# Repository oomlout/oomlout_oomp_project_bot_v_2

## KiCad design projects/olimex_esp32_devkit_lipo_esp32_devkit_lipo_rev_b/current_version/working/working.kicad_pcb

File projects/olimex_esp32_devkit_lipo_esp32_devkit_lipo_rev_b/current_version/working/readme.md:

# esp32_devkit_lipo
 
## summary 
* id: olimex_esp32_devkit_lipo_esp32_devkit_lipo_rev_b
* user: olimex
* name: esp32_devkit_lipo
* board: esp32_devkit_lipo_rev_b
* repo: https://github.com/OLIMEX/ESP32-DevKit-LiPo
* src_file_repo_kicad_pcb: HARDWARE/ESP32-DevKit-LiPo-Rev.B/ESP32-DevKit-Lipo_Rev_B.kicad_pcb
* src_file_repo_kicad_pcb_link: https://github.com/OLIMEX/ESP32-DevKit-LiPo/tree/master/HARDWARE/ESP32-DevKit-LiPo-Rev.B/ESP32-DevKit-Lipo_Rev_B.kicad_pcb

* src_file_repo_sch: HARDWARE/ESP32-DevKit-LiPo-Rev.B/ESP32-DevKit-Lipo_Rev_B.sch
* src_file_repo_sch_link: https://github.com/OLIMEX/ESP32-DevKit-LiPo/tree/master/HARDWARE/ESP32-DevKit-LiPo-Rev.B/ESP32-DevKit-Lipo_Rev_B.sch
* full details link: https://github.com/oomlout/oomlout_oomp_project_bot_v_2/tree/main/projects/olimex_esp32_devkit_lipo_esp32_devkit_lipo_rev_b/current_version/working

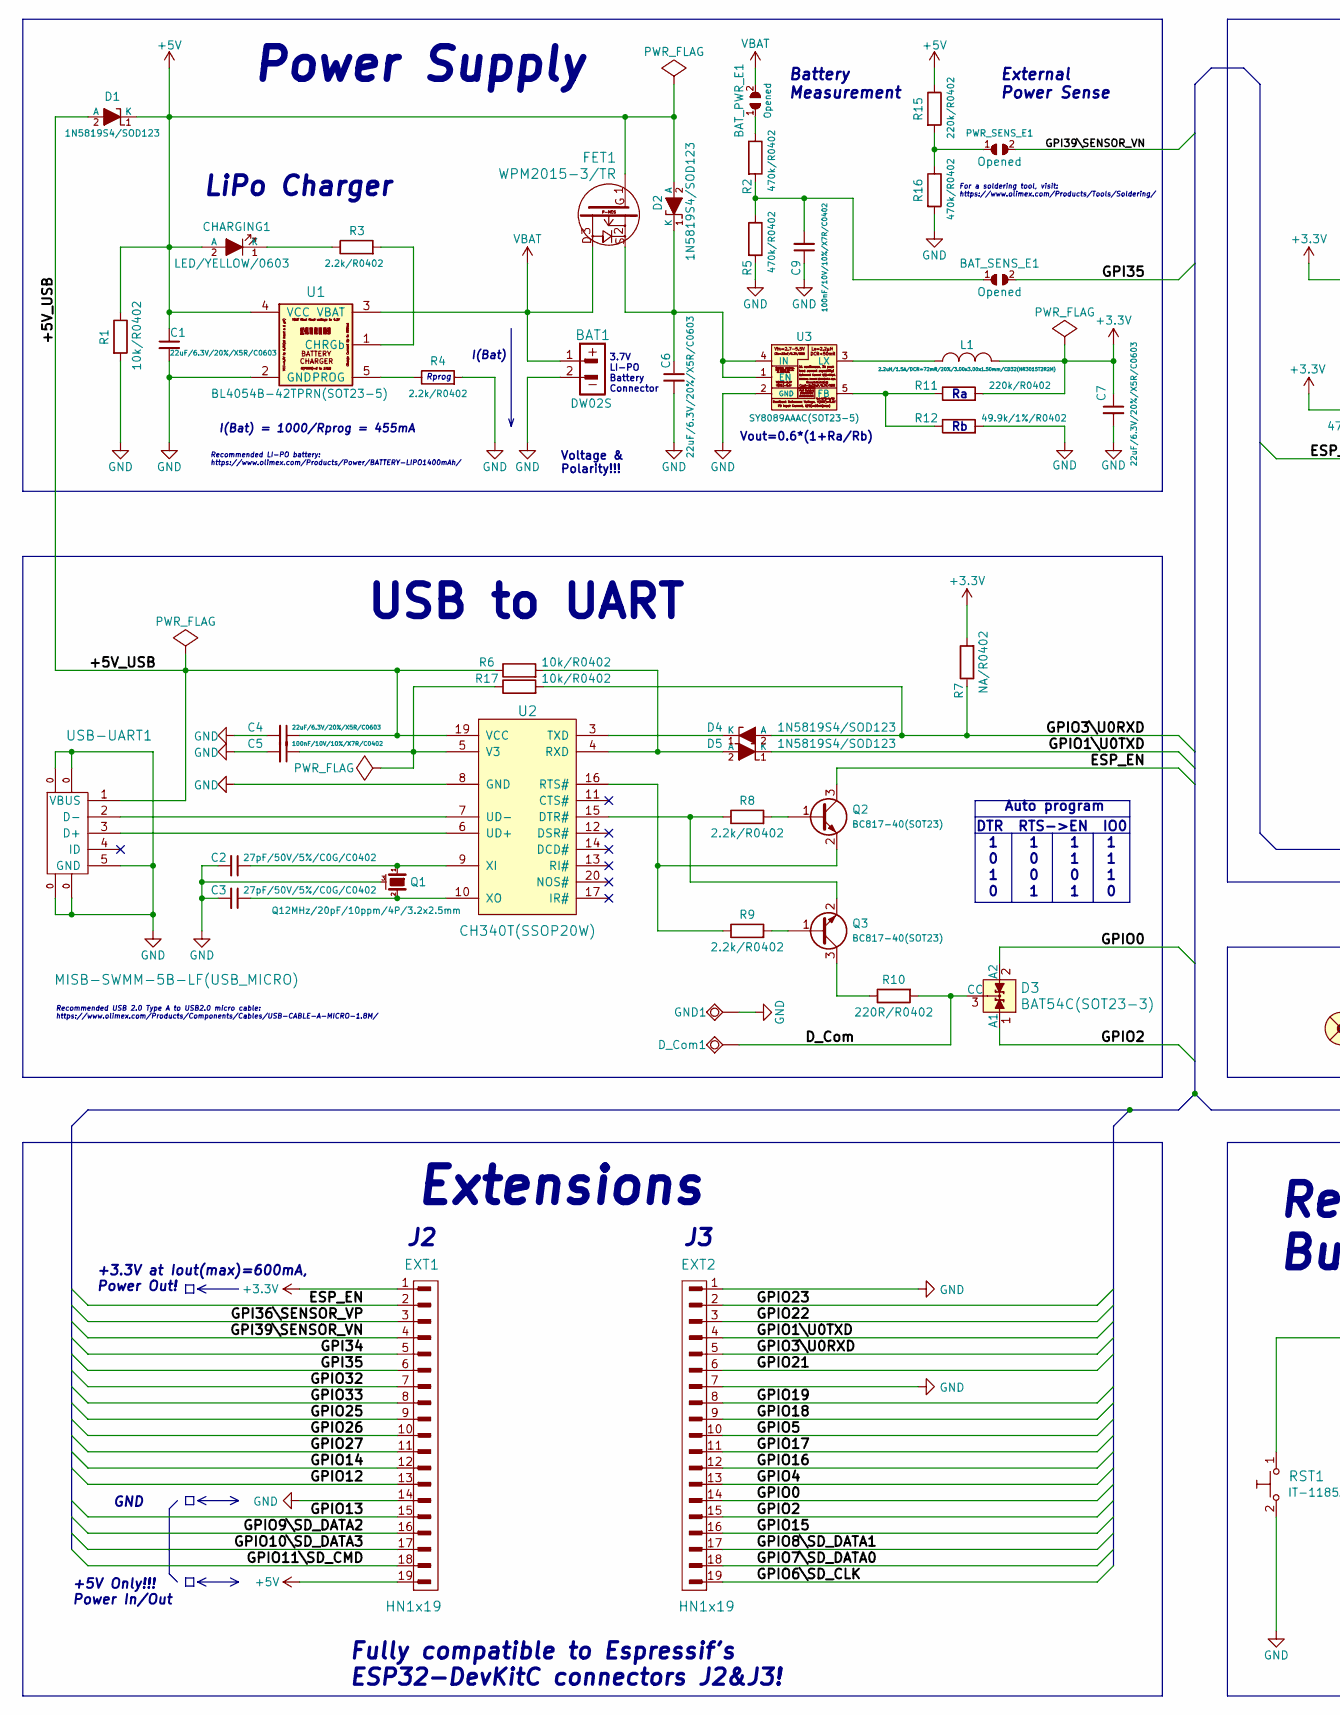
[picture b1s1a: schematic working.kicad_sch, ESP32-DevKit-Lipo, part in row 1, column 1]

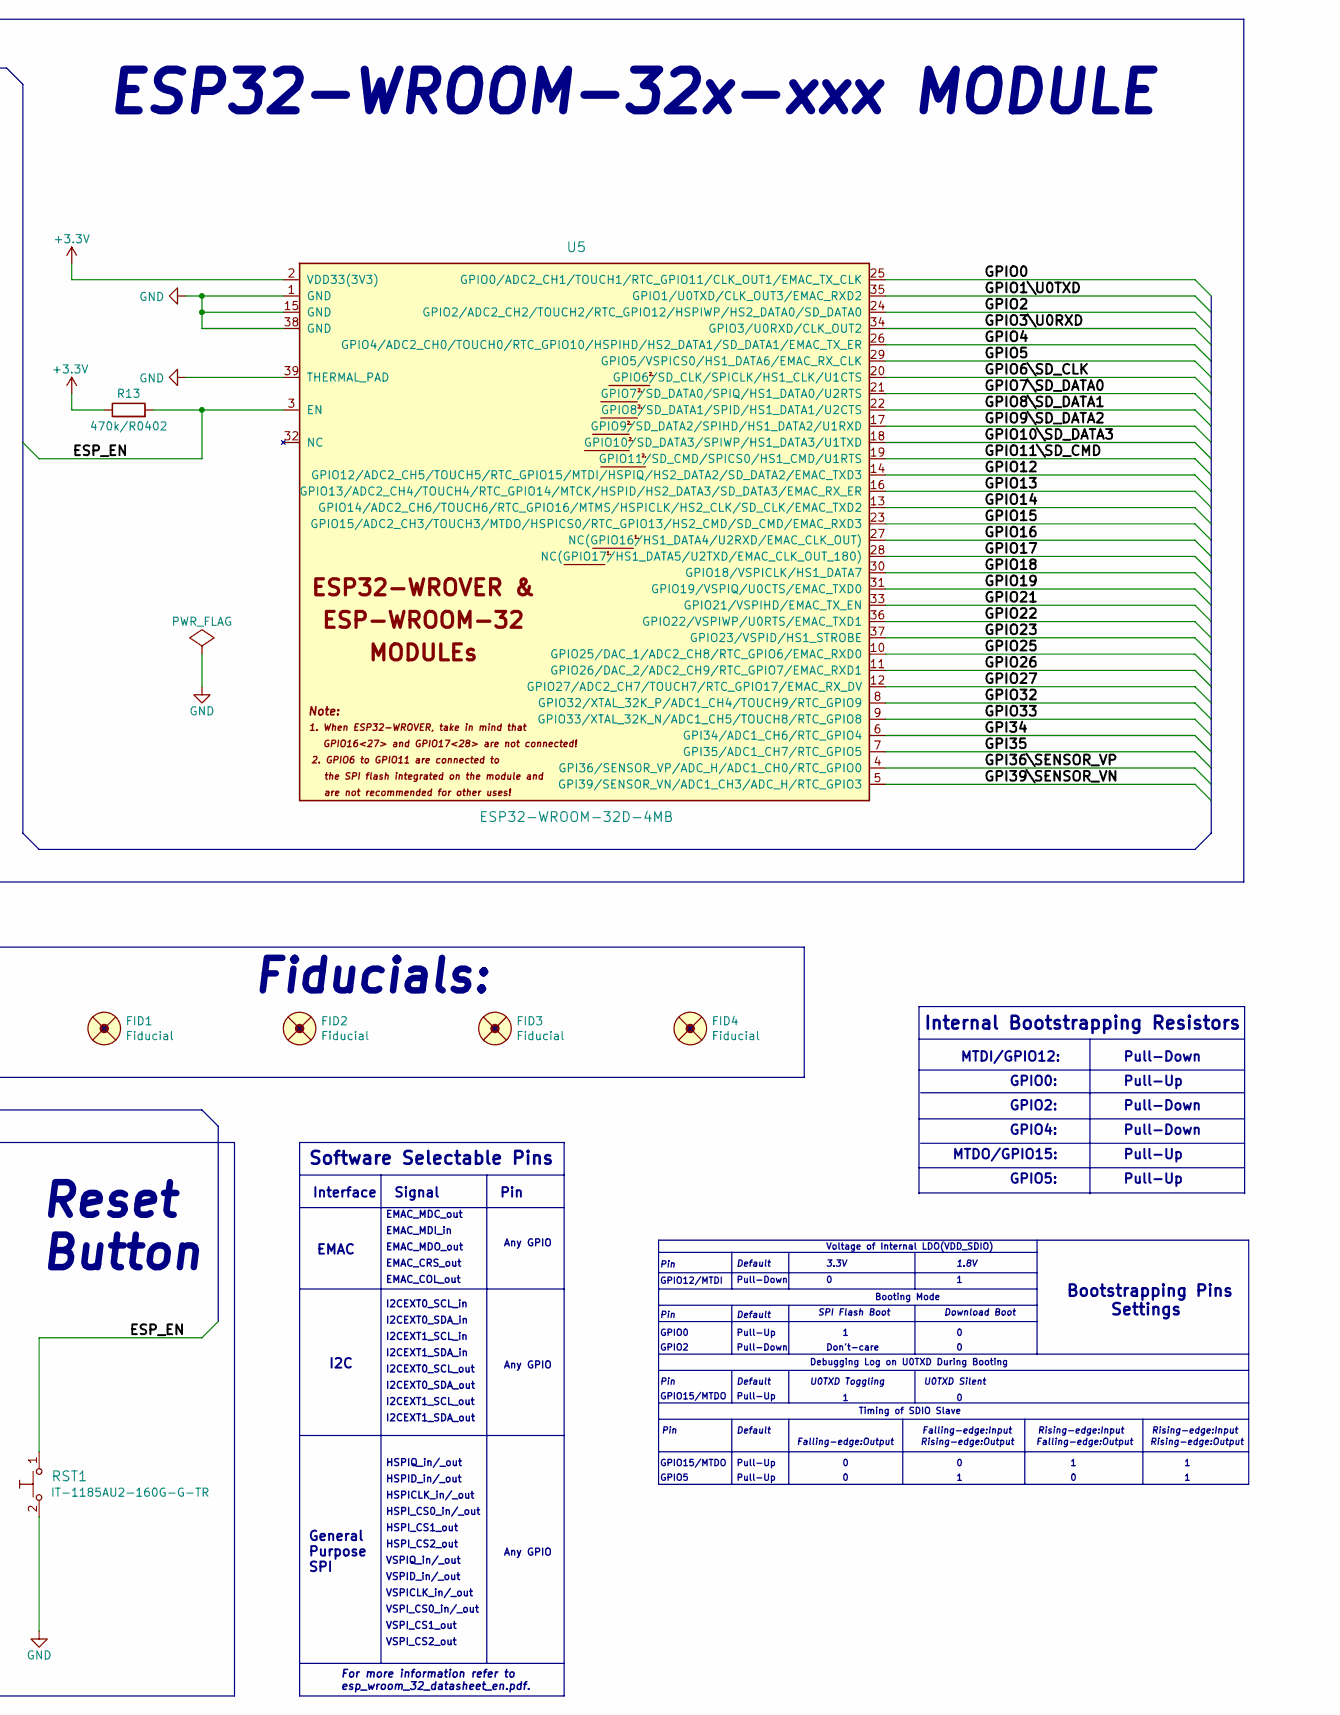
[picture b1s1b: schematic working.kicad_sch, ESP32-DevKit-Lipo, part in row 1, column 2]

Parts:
BAT1: DW02S; LIPO_BAT_VERTICAL_DW02S
BAT_PWR_E1: Opened; SJ_1_SMALLER
BAT_SENS_E1: Opened; SJ_1_SMALLER
C1, C4, C6, C7: 22uF/6.3V/20%/X5R/C0603; C_0603_5MIL_DWS
C2, C3: 27pF/50V/5%/C0G/C0402; C_0402_5MIL_DWS
C5, C9: 100nF/10V/10%/X7R/C0402; C_0402_5MIL_DWS
CHARGING1: LED/YELLOW/0603; LED_0603_KA
D1, D2, D4, D5: 1N5819S4/SOD123; SOD-123_1C-2A_KA
D3: BAT54C(SOT23-3); SOT23-3
D_Com1: TESTPAD; TESTPAD_40-ROUND
EXT1, EXT2: HN1x19
FET1: WPM2015-3/TR; SOT23
FID1, FID2, FID3, FID4: Fiducial; Fiducial1x3
GND1: TESTPAD; TESTPAD_40-ROUND
L1: 2.2uH/1.5A/DCR=72mR/20%/3.00x3.00x1.50mm/CD32(NR3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; CD32
PWR_SENS_E1: Opened; SJ_1_SMALLER
Q1: Q12MHz/20pF/10ppm/4P/3.2x2.5mm; TSX-3.2x2.5mm_GND(3)
Q2, Q3: BC817-40(SOT23); SOT23
R1, R6, R17: 10k/R0402; R_0402_5MIL_DWS
R2, R5, R13, R16: 470k/R0402; R_0402_5MIL_DWS
R3, R4, R8, R9: 2.2k/R0402; R_0402_5MIL_DWS
R7: NA/R0402; R_0402_5MIL_DWS
R10: 220R/R0402; R_0402_5MIL_DWS
R11, R15: 220k/R0402; R_0402_5MIL_DWS
R12: 49.9k/1%/R0402; R_0402_5MIL_DWS
RST1: IT-1185AU2-160G-G-TR; IT1185AU2_V2
U1: BL4054B-42TPRN(SOT23-5); SOT-23-5
U2: CH340T(SSOP20W); SSOP-20W
U3: SY8089AAAC(SOT23-5); SOT-23-5
U5: ESP32-WROOM-32D-4MB; ESP32-WROVER_MODULE
USB-UART1: MISB-SWMM-5B-LF(USB_MICRO); USB-MICRO_MISB-SWMM-5B_LF

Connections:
+3V3: C7.1, EXT1.1, L1.2, R7.2, R11.2, R13.1, U5.2 (VDD33(3V3))
+5V: C1.1, CHARGING1.2 (A), D1.1 (K), D2.2 (A), EXT1.19, FET1.1, R1.1, R15.1, U1.4 (VCC)
/+5V_USB: C4.1, D1.2 (A), R6.1, U2.19 (VCC), USB-UART1.1 (VBUS)
/D_Com: D3.3 (CC), D_Com1.1, R10.2
/ESP_EN: EXT1.2, Q2.3 (C), R13.2, RST1.1, U5.3 (EN)
/GPI34: EXT1.5, U5.6 (GPI34/ADC1_CH6/RTC_GPIO4)
/GPI35: BAT_SENS_E1.2, EXT1.6, U5.7 (GPI35/ADC1_CH7/RTC_GPIO5)
/GPI36\SENSOR_VP: EXT1.3, U5.4 (GPI36/SENSOR_VP/ADC_H/ADC1_CH0/RTC_GPIO0)
/GPI39\SENSOR_VN: EXT1.4, PWR_SENS_E1.2, U5.5 (GPI39/SENSOR_VN/ADC1_CH3/ADC_H/RTC_GPIO3)
/GPIO0: D3.2 (A2), EXT2.14, U5.25 (GPIO0/ADC2_CH1/TOUCH1/RTC_GPIO11/CLK_OU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)
/GPIO1\U0TXD: D5.1 (K), EXT2.4, U5.35 (GPIO1/U0TXD/CLK_OUT3/EMAC_RXD2)
/GPIO2: D3.1 (A1), EXT2.15, U5.24 (GPIO2/ADC2_CH2/TOUCH2/RTC_GPIO12/HSPIWP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)
/GPIO3\U0RXD: D4.2 (A), EXT2.5, R7.1, R17.2, U5.34 (GPIO3/U0RXD/CLK_OUT2)
/GPIO4: EXT2.13, U5.26 (GPIO4/ADC2_CH0/TOUCH0/RTC_GPIO10/HSPIHD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)
/GPIO5: EXT2.10, U5.29 (GPIO5/VSPICS0/HS1_DATA6/EMAC_RX_CLK)
/GPIO6\SD_CLK: EXT2.19, U5.20 (GPIO6/SD_CLK/SPICLK/HS1_CLK/U1CTS)
/GPIO7\SD_DATA0: EXT2.18, U5.21 (GPIO7/SD_DATA0/SPIQ/HS1_DATA0/U2RTS)
/GPIO8\SD_DATA1: EXT2.17, U5.22 (GPIO8/SD_DATA1/SPID/HS1_DATA1/U2CTS)
/GPIO9\SD_DATA2: EXT1.16, U5.17 (GPIO9/SD_DATA2/SPIHD/HS1_DATA2/U1RXD)
/GPIO10\SD_DATA3: EXT1.17, U5.18 (GPIO10/SD_DATA3/SPIWP/HS1_DATA3/U1TXD)
/GPIO11\SD_CMD: EXT1.18, U5.19 (GPIO11/SD_CMD/SPICS0/HS1_CMD/U1RTS)
/GPIO12: EXT1.13, U5.14 (GPIO12/ADC2_CH5/TOUCH5/RTC_GPIO15/MTDI/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)
/GPIO13: EXT1.15, U5.16 (GPIO13/ADC2_CH4/TOUCH4/RTC_GPIO14/MTCK/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)
/GPIO14: EXT1.12, U5.13 (GPIO14/ADC2_CH6/TOUCH6/RTC_GPIO16/MTMS/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)
/GPIO15: EXT2.16, U5.23 (GPIO15/ADC2_CH3/TOUCH3/MTDO/HSPICS0/RTC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)
/GPIO16: EXT2.12, U5.27 (NC(GPIO16/HS1_DATA4/U2RXD/EMAC_CLK_OUT))
/GPIO17: EXT2.11, U5.28 (NC(GPIO17/HS1_DATA5/U2TXD/EMAC_CLK_OUT_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)
/GPIO18: EXT2.9, U5.30 (GPIO18/VSPICLK/HS1_DATA7)
/GPIO19: EXT2.8, U5.31 (GPIO19/VSPIQ/U0CTS/EMAC_TXD0)
/GPIO21: EXT2.6, U5.33 (GPIO21/VSPIHD/EMAC_TX_EN)
/GPIO22: EXT2.3, U5.36 (GPIO22/VSPIWP/U0RTS/EMAC_TXD1)
/GPIO23: EXT2.2, U5.37 (GPIO23/VSPID/HS1_STROBE)
/GPIO25: EXT1.9, U5.10 (GPIO25/DAC_1/ADC2_CH8/RTC_GPIO6/EMAC_RX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)
/GPIO26: EXT1.10, U5.11 (GPIO26/DAC_2/ADC2_CH9/RTC_GPIO7/EMAC_RX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)
/GPIO27: EXT1.11, U5.12 (GPIO27/ADC2_CH7/TOUCH7/RTC_GPIO17/EMAC_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)
/GPIO32: EXT1.7, U5.8 (GPIO32/XTAL_32K_P/ADC1_CH4/TOUCH9/RTC_G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)
/GPIO33: EXT1.8, U5.9 (GPIO33/XTAL_32K_N/ADC1_CH5/TOUCH8/RTC_G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)
GND: BAT1.2, C1.2, C2.2, C3.2, C4.2, C5.2, C6.2, C7.2, C9.1, EXT1.14, EXT2.1, EXT2.7, GND1.1, Q1.3 (case), R1.2, R4.2, R5.2, R12.2, R16.2, RST1.2, U1.2 (GND), U2.8 (GND), U3.2 (GND), U5.1 (GND), U5.15 (GND), U5.38 (GND), U5.39 (THERMAL_PAD), USB-UART1.0, USB-UART1.5 (GND)
unnamed: BAT_PWR_E1.1, R2.1
unnamed: BAT_SENS_E1.1, C9.2, R2.2, R5.1
unnamed: C2.1, Q1.1, U2.9 (XI)
unnamed: C3.1, Q1.2, U2.10 (XO)
unnamed: C5.1, R17.1, U2.5 (V3)
unnamed: C6.1, D2.1 (K), FET1.2, U3.1 (EN), U3.4 (IN)
unnamed: CHARGING1.1 (K), R3.1
unnamed: D4.1 (K), U2.3 (TXD)
unnamed: D5.2 (A), R6.2, U2.4 (RXD)
unnamed: L1.1, U3.3 (LX)
unnamed: PWR_SENS_E1.1, R15.2, R16.1
unnamed: Q2.1 (B), R8.2
unnamed: Q2.2 (E), R9.1, U2.16 (RTS#)
unnamed: Q3.1 (B), R9.2
unnamed: Q3.2 (E), R8.1, U2.15 (DTR#)
unnamed: Q3.3 (C), R10.1
unnamed: R3.2, U1.1 (CHRGb)
unnamed: R4.1, U1.5 (PROG)
unnamed: R11.1, R12.1, U3.5 (FB)
unnamed: U2.6 (UD+), USB-UART1.3 (D+)
unnamed: U2.7 (UD-), USB-UART1.2 (D-)
VBAT: BAT1.1, BAT_PWR_E1.2, FET1.3, U1.3 (VBAT)

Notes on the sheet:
I2CEXT1_SDA_in
Extensions
Pull-Up
Pull-Down
GPIO5
I(Bat)
GPIO15/MTDO
MTDO/GPIO15:
GPIO12/MTDI
Booting Mode
Interface
HSPID_in/_out
Default
Pin
GPIO5:
Internal Bootstrapping Resistors
Timing of SDIO Slave
EMAC_MDO_out
Rprog
VSPI_CS2_out
I2CEXT1_SCL_in
MTDI/GPIO12:
Falling-edge:Output
Bootstrapping Pins Settings
Auto program
Any GPIO
EMAC_CRS_out
Voltage & Polarity!!!
VSPI_CS1_out
Power Supply
EMAC_MDI_in
+3.3V at Iout(max)=600mA, Power Out!
+5V Only!!! Power In/Out
HSPI_CS2_out
HSPIQ_in/_out
Debugging Log on U0TXD During Booting
GPIO4:
I2CEXT0_SDA_out
I2CEXT1_SDA_out
HSPICLK_in/_out

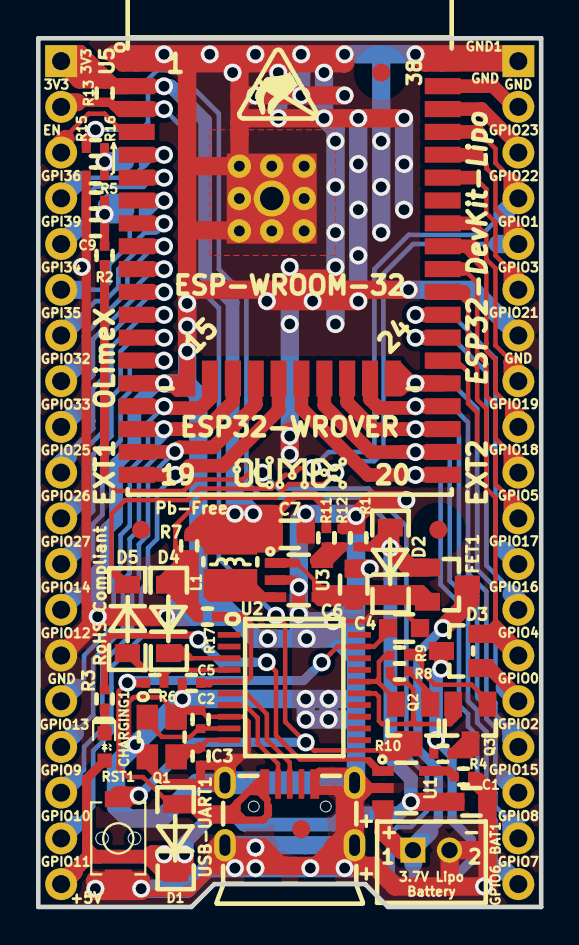
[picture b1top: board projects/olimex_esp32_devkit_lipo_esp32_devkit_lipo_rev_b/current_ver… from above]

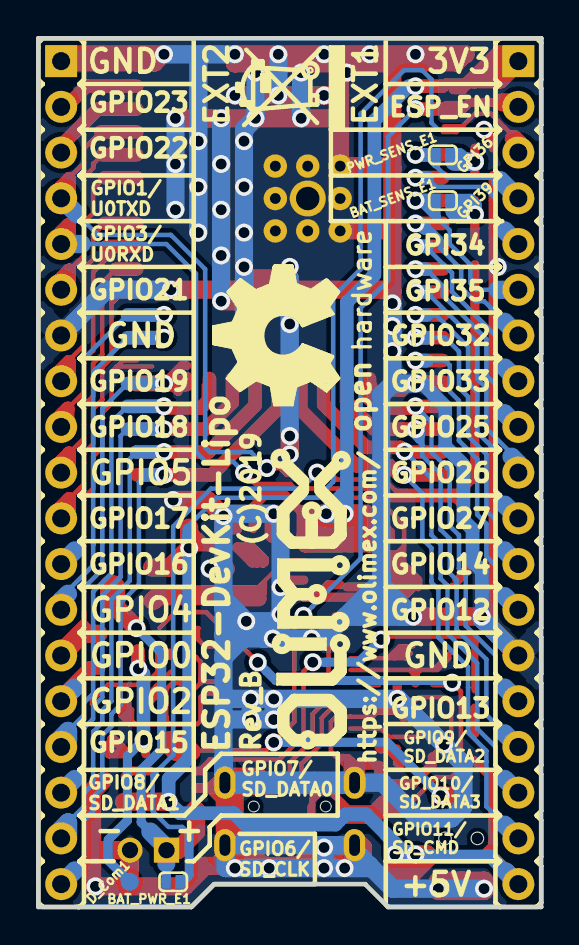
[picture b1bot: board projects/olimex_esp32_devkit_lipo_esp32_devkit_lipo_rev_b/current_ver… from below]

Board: 2 copper layers, 27.9 x 48.3 mm, 58 parts (9 on the bottom side), 60 nets.

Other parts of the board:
Logo_OSHW: LOGO_OPENHARDWARE_8x8
Olimex_Logo_Big: OLIMEX_LOGO_TB
Olimex_Logo_Small: LOGO_OLIMEX_80
Sign_Antistatic: Val**; LOGO_ANTISTATIC_SMALL_4.5mmX2.8mm
Sign_RecycleBin: LOGO_RECYCLEBIN_1

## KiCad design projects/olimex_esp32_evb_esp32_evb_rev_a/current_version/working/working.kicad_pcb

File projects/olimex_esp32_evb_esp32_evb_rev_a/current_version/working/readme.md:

# esp32_evb
 
## summary 
* id: olimex_esp32_evb_esp32_evb_rev_a
* user: olimex
* name: esp32_evb
* board: esp32_evb_rev_a
* repo: https://github.com/OLIMEX/ESP32-EVB
* src_file_repo_kicad_pcb: HARDWARE/REV-A/ESP32-EVB_Rev_A.kicad_pcb
* src_file_repo_kicad_pcb_link: https://github.com/OLIMEX/ESP32-EVB/tree/master/HARDWARE/REV-A/ESP32-EVB_Rev_A.kicad_pcb

* src_file_repo_sch: HARDWARE/REV-A/ESP32-EVB_Rev_A.sch
* src_file_repo_sch_link: https://github.com/OLIMEX/ESP32-EVB/tree/master/HARDWARE/REV-A/ESP32-EVB_Rev_A.sch
* full details link: https://github.com/oomlout/oomlout_oomp_project_bot_v_2/tree/main/projects/olimex_esp32_evb_esp32_evb_rev_a/current_version/working

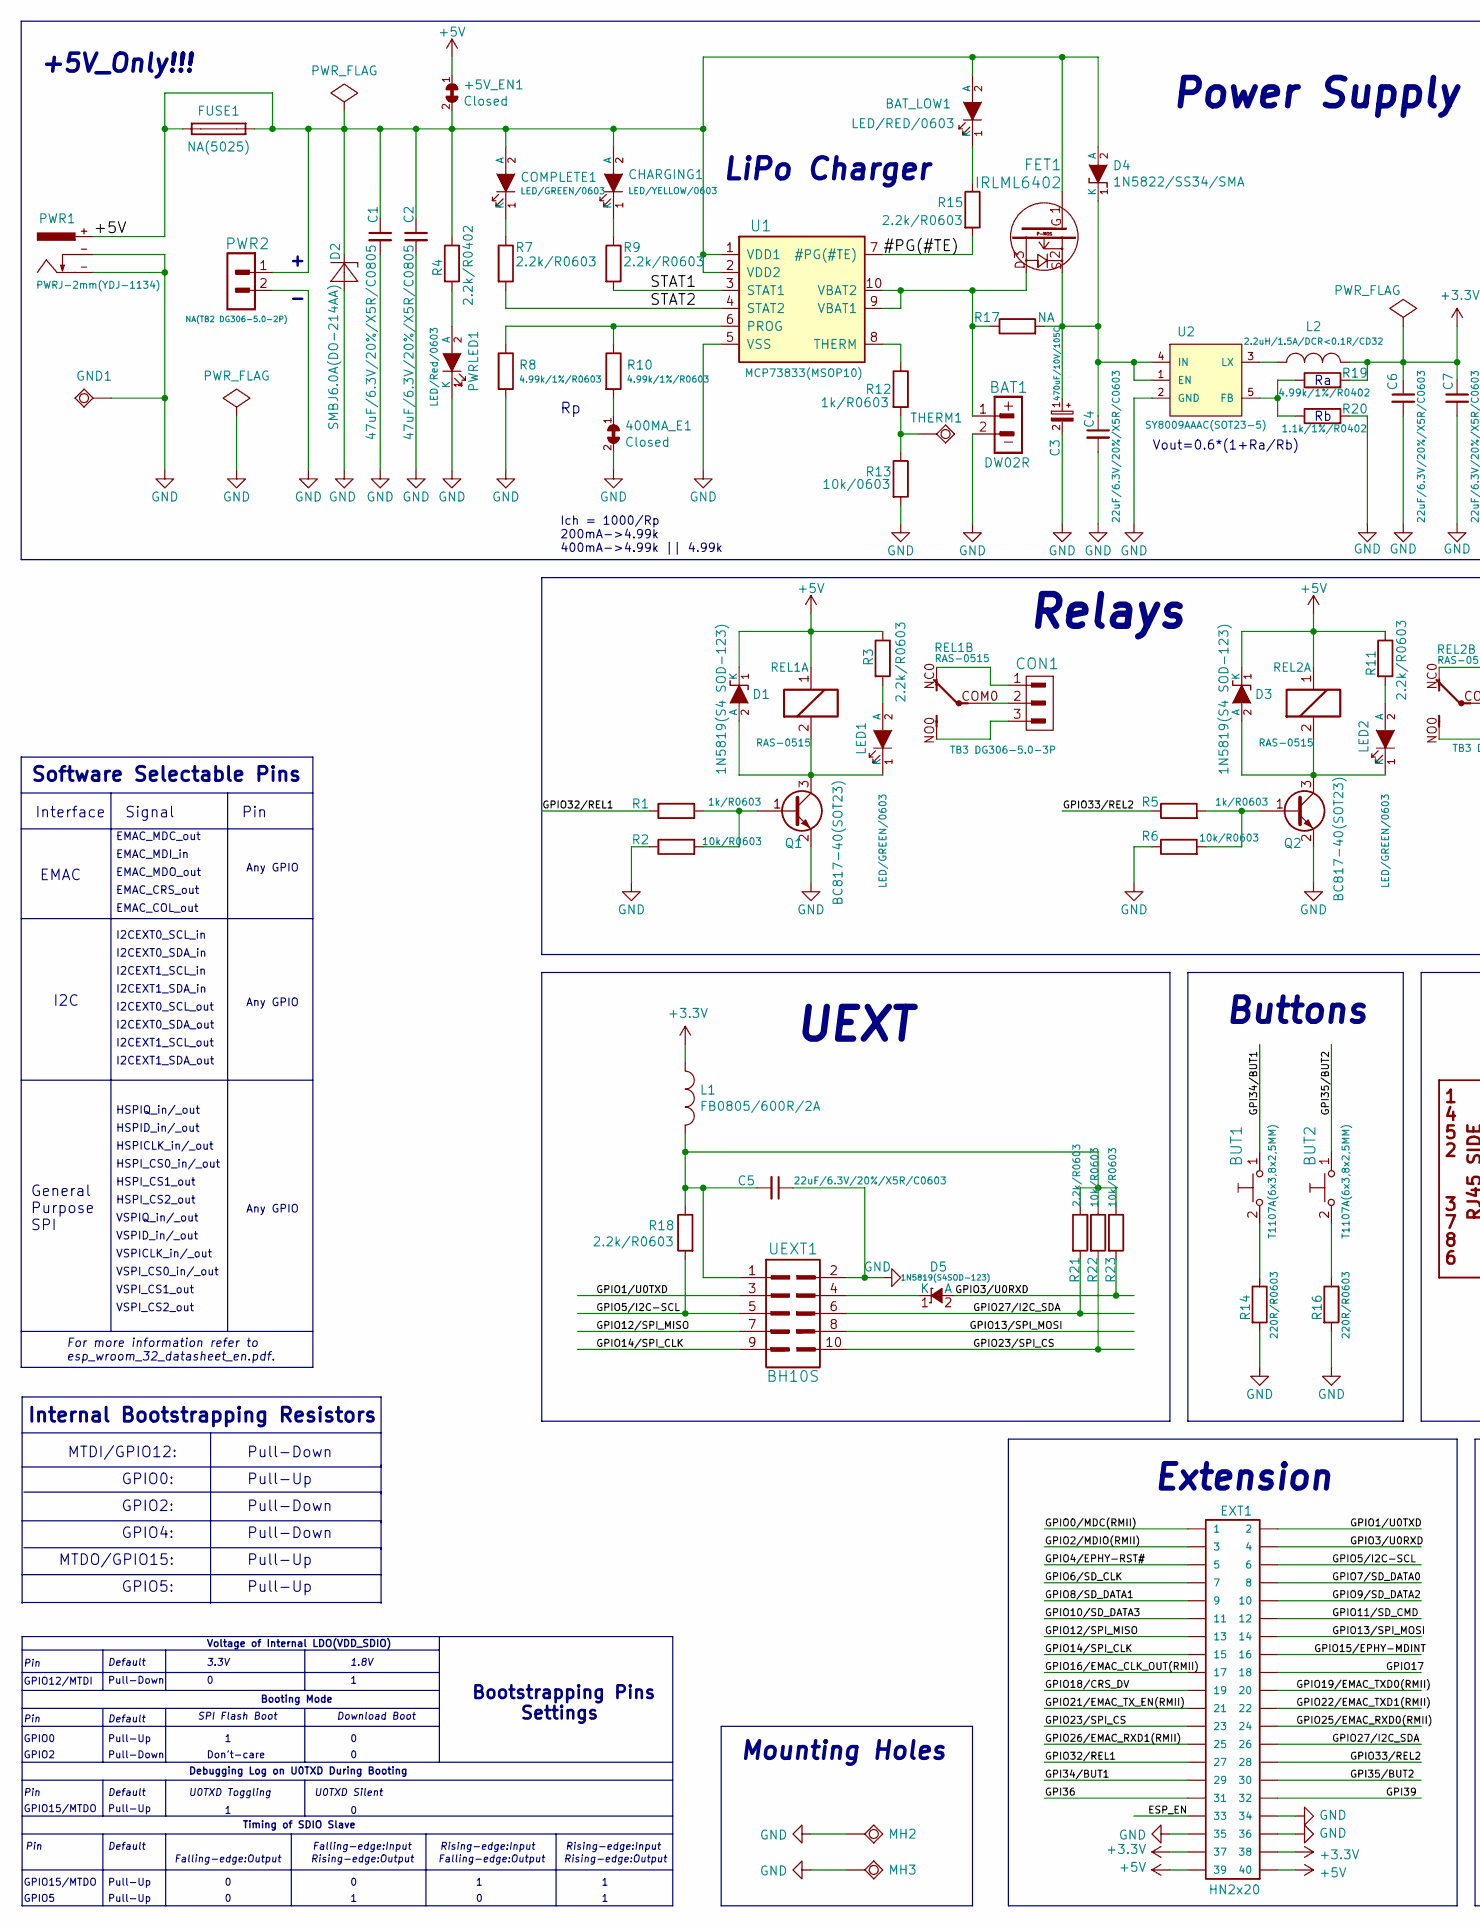
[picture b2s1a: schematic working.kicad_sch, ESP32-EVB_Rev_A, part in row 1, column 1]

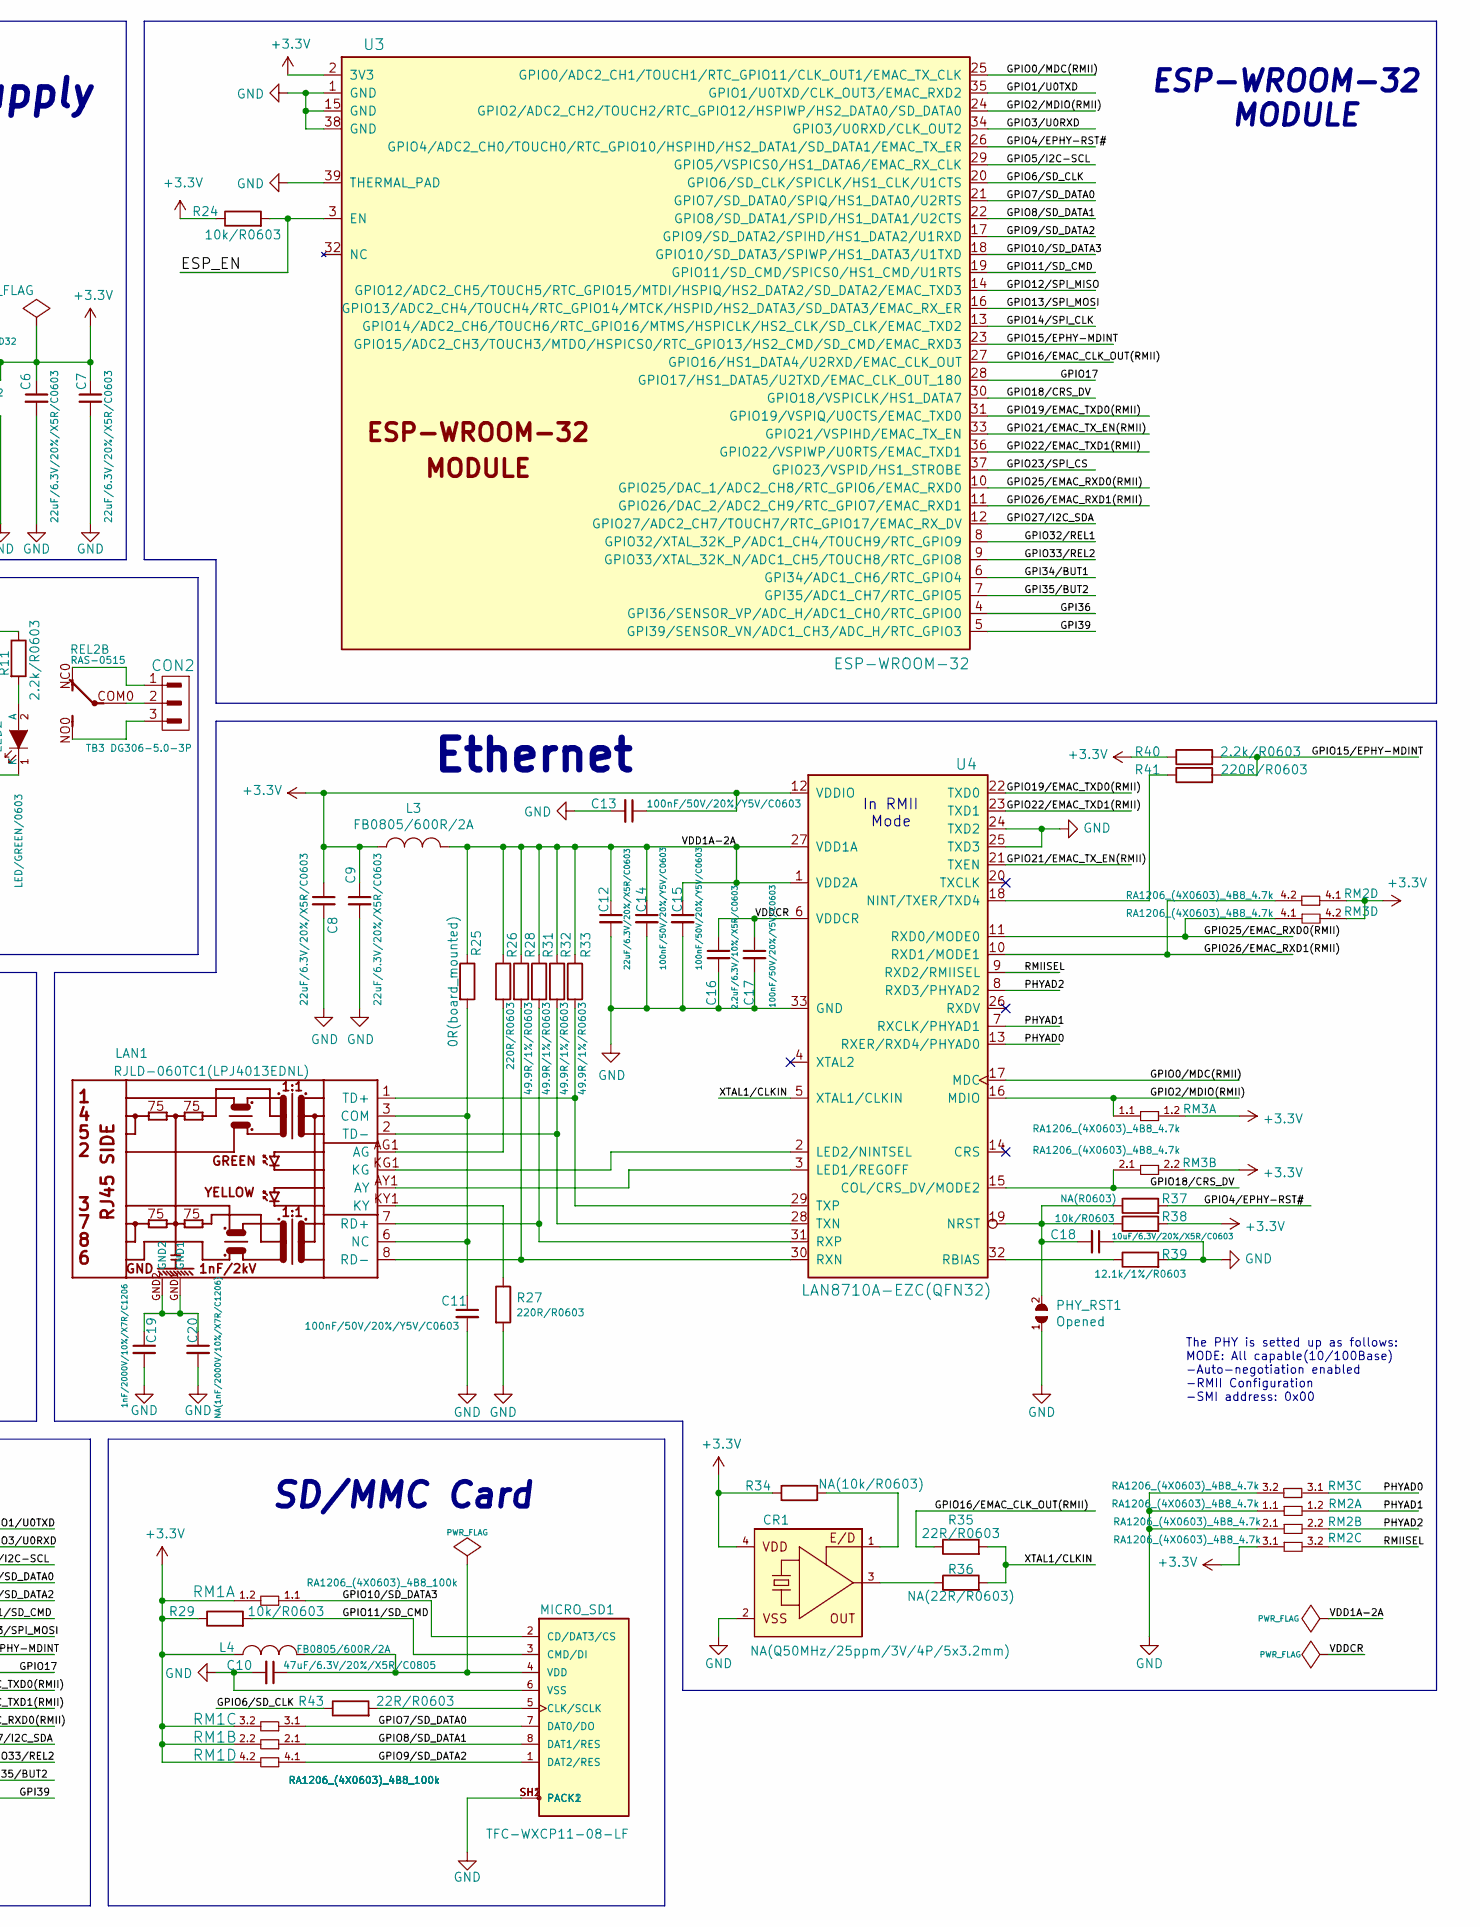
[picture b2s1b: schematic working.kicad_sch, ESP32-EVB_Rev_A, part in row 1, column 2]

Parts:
400MA_E1: Closed; SJ_Closed
+5V_EN1: Closed; SJ_Closed
BAT1: DW02R; LIPO_BAT-CON2DW02R
BAT_LOW1: LED/RED/0603; LED_0603_KA
BUT1, BUT2: T1107A(6x3,8x2,5MM)
C1, C2, C10: 47uF/6.3V/20%/X5R/C0805; C_0805_5MIL_DWS
C3: 470uF/10V/105C; CPOL-EUE2.5-6.3(CPOL-EU)
C4, C5, C6, C7, C8, C9, C12: 22uF/6.3V/20%/X5R/C0603; C_0603_5MIL_DWS
C11, C13, C14, C15, C17: 100nF/50V/20%/Y5V/C0603; C_0603_5MIL_DWS
C16: 2.2uF/6.3V/10%/X5R/C0603; C_0603_5MIL_DWS
C18: 10uF/6.3V/20%/X5R/C0603; C_0603_5MIL_DWS
C19: 1nF/2000V/10%/X7R/C1206; C_1206_5MIL_DWS_ISO
C20: NA(1nF/2000V/10%/X7R/C1206); C_1206_5MIL_DWS_ISO
CHARGING1: LED/YELLOW/0603; LED_0603_KA
COMPLETE1: LED/GREEN/0603; LED_0603_KA
CON1, CON2: TB3 DG306-5.0-3P; TB3-DG306-5.0_3P
CR1: NA(Q50MHz/25ppm/3V/4P/5x3.2mm); 5032-4P_HCX-3S
D1, D3: 1N5819(S4 SOD-123); SOD-123_1C-2A_KA
D2: SMBJ6.0A(DO-214AA); DO214AA
D4: 1N5822/SS34/SMA; SMA-KA
D5: 1N5819(S4SOD-123); SOD-123_1C-2A_KA
EXT1: HN2x20
FET1: IRLML6402; SOT23
FUSE1: NA(5025); FUSE-5025
GND1: TESTPAD; TESTPAD_40-ROUND
L1, L3, L4: FB0805/600R/2A; L_0805_5MIL_DWS
L2: 2.2uH/1.5A/DCR<0.1R/CD32; CD32
LAN1: RJLD-060TC1(LPJ4013EDNL); RJLBC-060TC1
LED1, LED2: LED/GREEN/0603; LED_0603_KA
MH2, MH3: Mounting_hole_Shield_3.3mm
MICRO_SD1: TFC-WXCP11-08-LF
PHY_RST1: Opened; SJ
PWR1: PWRJ-2mm(YDJ-1134); PWRJ-2mm(YDJ-1136)
PWR2: NA(TB2 DG306-5.0-2P); TB2-DG306-5.0_2P
PWRLED1: LED/Red/0603; LED_0603_KA
Q1, Q2: BC817-40(SOT23); SOT23
R1, R5, R12: 1k/R0603; R_0603_5MIL_DWS
R2, R6, R22, R23, R24, R29, R38: 10k/R0603; R_0603_5MIL_DWS
R3, R7, R9, R11, R15, R18, R21, R40: 2.2k/R0603; R_0603_5MIL_DWS
R4: 2.2k/R0402; R_0402_5MIL_DWS
R8, R10: 4.99k/1%/R0603; R_0603_5MIL_DWS
R13: 10k/0603; R_0603_5MIL_DWS
R14, R16, R26, R27, R41: 220R/R0603; R_0603_5MIL_DWS
R17: NA; R_0603_5MIL_DWS
R19: 4.99k/1%/R0402; R_0402_5MIL_DWS
R20: 1.1k/1%/R0402; R_0402_5MIL_DWS
R25: 0R(board_mounted); 0R_0603
R28, R31, R32, R33: 49.9R/1%/R0603; R_0603_5MIL_DWS
R34: NA(10k/R0603); R_0603_5MIL_DWS
R35, R43: 22R/R0603; R_0603_5MIL_DWS
R36: NA(22R/R0603); R_0603_5MIL_DWS
R37: NA(R0603); R_0603_5MIL_DWS
R39: 12.1k/1%/R0603; R_0603_5MIL_DWS
REL1, REL2: RAS-0515; Relay_RAS-05-15
RM1: RA1206_(4X0603)_4B8_100k; R_MATRIX_4
RM2, RM3: RA1206_(4X0603)_4B8_4.7k; R_MATRIX_4
THERM1: TESTPAD; TESTPAD_40-ROUND
U1: MCP73833(MSOP10); MSOP-10_Pitch-0.5mm_3.00x3.00x1.00mm
U2: SY8009AAAC(SOT23-5); SOT-23-5
U3: ESP-WROOM-32; ESP-WROOM-32_MODULE
U4: LAN8710A-EZC(QFN32); QFN32_EP(33)_5.00x5.00x0.90mm_Pitch_0.50mm
UEXT1: BH10S; UEXT_ML10

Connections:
+3V3: C6.1, C7.1, C8.1, C9.1, C13.1, CR1.4 (VDD), EXT1.37, EXT1.38, L1.1, L2.2, L3.1, L4.1, R19.2, R24.1, R29.1, R34.1, R38.2, R40.1, RM1.1.2, RM1.2.2, RM1.3.2, RM1.4.2, RM2.3.1, RM2.4.1, RM3.1.2, RM3.2.2, RM3.4.2, U3.2 (3V3), U4.12 (VDDIO)
+5V: +5V_EN1.1, +5V_EN1.2, BAT_LOW1.2 (A), C1.1, C2.1, CHARGING1.2 (A), COMPLETE1.2 (A), D1.1 (K), D2.C, D3.1 (K), D4.2 (A), EXT1.39, EXT1.40, FET1.1, FUSE1.1, FUSE1.2, PWR1.+, PWR2.1, R3.1, R4.1, R11.1, REL1.1, REL2.1, U1.1 (VDD1), U1.2 (VDD2)
/#PG(#TE): R15.2, U1.7 (#PG(#TE))
/ESP_EN: EXT1.33, R24.2, U3.3 (EN)
/GPI34/BUT1: BUT1.1, EXT1.29, U3.6 (GPI34/ADC1_CH6/RTC_GPIO4)
/GPI35/BUT2: BUT2.1, EXT1.30, U3.7 (GPI35/ADC1_CH7/RTC_GPIO5)
/GPI36: EXT1.31, U3.4 (GPI36/SENSOR_VP/ADC_H/ADC1_CH0/RTC_GPIO0)
/GPI39: EXT1.32, U3.5 (GPI39/SENSOR_VN/ADC1_CH3/ADC_H/RTC_GPIO3)
/GPIO0/MDC(RMII): EXT1.1, U3.25 (GPIO0/ADC2_CH1/TOUCH1/RTC_GPIO11/CLK_OU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), U4.17 (MDC)
/GPIO1/U0TXD: EXT1.2, U3.35 (GPIO1/U0TXD/CLK_OUT3/EMAC_RXD2), UEXT1.3
/GPIO2/MDIO(RMII): EXT1.3, RM3.1.1, U3.24 (GPIO2/ADC2_CH2/TOUCH2/RTC_GPIO12/HSPIWP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), U4.16 (MDIO)
/GPIO3/U0RXD: D5.2 (A), EXT1.4, R23.2, U3.34 (GPIO3/U0RXD/CLK_OUT2)
/GPIO4/EPHY-RST#: EXT1.5, R37.2, U3.26 (GPIO4/ADC2_CH0/TOUCH0/RTC_GPIO10/HSPIHD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)
/GPIO5/I2C-SCL: EXT1.6, R18.2, U3.29 (GPIO5/VSPICS0/HS1_DATA6/EMAC_RX_CLK), UEXT1.5
/GPIO6/SD_CLK: EXT1.7, R43.1, U3.20 (GPIO6/SD_CLK/SPICLK/HS1_CLK/U1CTS)
/GPIO7/SD_DATA0: EXT1.8, MICRO_SD1.7 (DAT0/DO), RM1.3.1, U3.21 (GPIO7/SD_DATA0/SPIQ/HS1_DATA0/U2RTS)
/GPIO8/SD_DATA1: EXT1.9, MICRO_SD1.8 (DAT1/RES), RM1.2.1, U3.22 (GPIO8/SD_DATA1/SPID/HS1_DATA1/U2CTS)
/GPIO9/SD_DATA2: EXT1.10, MICRO_SD1.1 (DAT2/RES), RM1.4.1, U3.17 (GPIO9/SD_DATA2/SPIHD/HS1_DATA2/U1RXD)
/GPIO10/SD_DATA3: EXT1.11, MICRO_SD1.2 (CD/DAT3/CS), RM1.1.1, U3.18 (GPIO10/SD_DATA3/SPIWP/HS1_DATA3/U1TXD)
/GPIO11/SD_CMD: EXT1.12, MICRO_SD1.3 (CMD/DI), R29.2, U3.19 (GPIO11/SD_CMD/SPICS0/HS1_CMD/U1RTS)
/GPIO12/SPI_MISO: EXT1.13, U3.14 (GPIO12/ADC2_CH5/TOUCH5/RTC_GPIO15/MTDI/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), UEXT1.7
/GPIO13/SPI_MOSI: EXT1.14, U3.16 (GPIO13/ADC2_CH4/TOUCH4/RTC_GPIO14/MTCK/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), UEXT1.8
/GPIO14/SPI_CLK: EXT1.15, U3.13 (GPIO14/ADC2_CH6/TOUCH6/RTC_GPIO16/MTMS/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), UEXT1.9
/GPIO15/EPHY-MDINT: EXT1.16, R40.2, R41.2, U3.23 (GPIO15/ADC2_CH3/TOUCH3/MTDO/HSPICS0/RTC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)
/GPIO16/EMAC_CLK_OUT(RMII): EXT1.17, R35.1, U3.27 (GPIO16/HS1_DATA4/U2RXD/EMAC_CLK_OUT)
/GPIO17: EXT1.18, U3.28 (GPIO17/HS1_DATA5/U2TXD/EMAC_CLK_OUT_180)
/GPIO18/CRS_DV: EXT1.19, RM3.2.1, U3.30 (GPIO18/VSPICLK/HS1_DATA7), U4.15 (COL/CRS_DV/MODE2)
/GPIO19/EMAC_TXD0(RMII): EXT1.20, U3.31 (GPIO19/VSPIQ/U0CTS/EMAC_TXD0), U4.22 (TXD0)
/GPIO21/EMAC_TX_EN(RMII): EXT1.21, U3.33 (GPIO21/VSPIHD/EMAC_TX_EN), U4.21 (TXEN)
/GPIO22/EMAC_TXD1(RMII): EXT1.22, U3.36 (GPIO22/VSPIWP/U0RTS/EMAC_TXD1), U4.23 (TXD1)
/GPIO23/SPI_CS: EXT1.23, R22.2, U3.37 (GPIO23/VSPID/HS1_STROBE), UEXT1.10
/GPIO25/EMAC_RXD0(RMII): EXT1.24, RM3.4.1, U3.10 (GPIO25/DAC_1/ADC2_CH8/RTC_GPIO6/EMAC_RX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), U4.11 (RXD0/MODE0)
/GPIO26/EMAC_RXD1(RMII): EXT1.25, RM2.4.2, U3.11 (GPIO26/DAC_2/ADC2_CH9/RTC_GPIO7/EMAC_RX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), U4.10 (RXD1/MODE1)
/GPIO27/I2C_SDA: EXT1.26, R21.2, U3.12 (GPIO27/ADC2_CH7/TOUCH7/RTC_GPIO17/EMAC_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), UEXT1.6
/GPIO32/REL1: EXT1.27, R1.1, U3.8 (GPIO32/XTAL_32K_P/ADC1_CH4/TOUCH9/RTC_G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)
/GPIO33/REL2: EXT1.28, R5.1, U3.9 (GPIO33/XTAL_32K_N/ADC1_CH5/TOUCH8/RTC_G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)
/PHYAD0: RM3.3.1, U4.13 (RXER/RXD4/PHYAD0)
/PHYAD1: RM2.1.2, U4.7 (RXCLK/PHYAD1)
/PHYAD2: RM2.2.2, U4.8 (RXD3/PHYAD2)
/RMIISEL: RM2.3.2, U4.9 (RXD2/RMIISEL)
/STAT1: R9.2, U1.3 (STAT1)
/STAT2: R7.2, U1.4 (STAT2)
/VDD1A-2A: C12.1, C14.1, C15.1, L3.2, R25.1, R26.1, R28.1, R31.1, R32.1, R33.1, U4.1 (VDD2A), U4.27 (VDD1A)
/VDDCR: C16.1, C17.1, U4.6 (VDDCR)
/XTAL1/CLKIN: R35.2, R36.2, U4.5 (XTAL1/CLKIN)
GND: 400MA_E1.2, BAT1.2, C1.2, C2.2, C3.2 (-), C4.2, C5.1, C6.2, C7.2, C8.2, C9.2, C10.2, C11.2, C12.2, C13.2, C14.2, C15.2, C16.2, C17.2, C18.1, C19.2, C20.2, CR1.2 (VSS), D2.A, EXT1.34, EXT1.35, EXT1.36, GND1.1, MH2.GND1, MH3.GND1, MICRO_SD1.6 (VSS), MICRO_SD1.SH1 (PACK1), MICRO_SD1.SH2 (PACK2), PHY_RST1.1, PWR1.-, PWR2.2, PWRLED1.1 (K), Q1.2 (E), Q2.2 (E), R2.1, R6.1, R8.2, R13.2, R14.2, R16.2, R20.2, R27.2, R39.2, RM2.1.1, RM2.2.1, RM3.3.2, U1.5 (VSS), U2.2 (GND), U3.1 (GND), U3.15 (GND), U3.38 (GND), U3.39 (THERMAL_PAD), U4.24 (TXD2), U4.25 (TXD3), U4.33 (GND), UEXT1.2
unnamed: 400MA_E1.1, R10.2
unnamed: BAT1.1, FET1.3, R17.1, U1.9 (VBAT1), U1.10 (VBAT2)
unnamed: BAT_LOW1.1 (K), R15.1
unnamed: BUT1.2, R14.1
unnamed: BUT2.2, R16.1
unnamed: C3.1 (+), C4.1, D4.1 (K), FET1.2, R17.2, U2.1 (EN), U2.4 (IN)
unnamed: C5.2, L1.2, R18.1, R21.1, R22.1, R23.1, UEXT1.1
unnamed: C10.1, L4.2, MICRO_SD1.4 (VDD)
unnamed: C11.1, LAN1.3 (COM), LAN1.6 (NC), R25.2
unnamed: C18.2, PHY_RST1.2, R37.1, R38.1, U4.19 (NRST)
unnamed: C19.1, C20.1, LAN1.GND1, LAN1.GND2
unnamed: CHARGING1.1 (K), R9.1
unnamed: COMPLETE1.1 (K), R7.1
unnamed: CON1.1, REL1.NC0
unnamed: CON1.2, REL1.COM0
unnamed: CON1.3, REL1.NO0
unnamed: CON2.1, REL2.NC0
unnamed: CON2.2, REL2.COM0
unnamed: CON2.3, REL2.NO0
unnamed: CR1.1 (E/D), R34.2
unnamed: CR1.3 (OUT), R36.1
unnamed: D1.2 (A), LED1.1 (K), Q1.3 (C), REL1.2
unnamed: D3.2 (A), LED2.1 (K), Q2.3 (C), REL2.2
unnamed: D5.1 (K), UEXT1.4
unnamed: L2.1, U2.3 (LX)
unnamed: LAN1.1 (TD+), R33.2, U4.29 (TXP)
unnamed: LAN1.2 (TD-), R32.2, U4.28 (TXN)
unnamed: LAN1.7 (RD+), R31.2, U4.31 (RXP)
unnamed: LAN1.8 (RD-), R28.2, U4.30 (RXN)
unnamed: LAN1.AG1 (AG), R26.2
unnamed: LAN1.AY1 (AY), U4.3 (LED1/REGOFF)
unnamed: LAN1.KG1 (KG), U4.2 (LED2/NINTSEL)
unnamed: LAN1.KY1 (KY), R27.1
unnamed: LED1.2 (A), R3.2
unnamed: LED2.2 (A), R11.2
unnamed: MICRO_SD1.5 (CLK/SCLK), R43.2
unnamed: PWRLED1.2 (A), R4.2
unnamed: Q1.1 (B), R1.2, R2.2
unnamed: Q2.1 (B), R5.2, R6.2
unnamed: R8.1, R10.1, U1.6 (PROG)
unnamed: R12.1, U1.8 (THERM)
unnamed: R12.2, R13.1, THERM1.1
unnamed: R19.1, R20.1, U2.5 (FB)
unnamed: R39.1, U4.32 (RBIAS)
unnamed: R41.1, U4.18 (NINT/TXER/TXD4)

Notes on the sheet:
Pin
Pull-Down
GPIO0:
Pull-Up
I2CEXT0_SDA_out
GPIO5:
Any GPIO
HSPI_CS1_out
Default
I2CEXT1_SDA_in
Booting Mode
Rising-edge:Output
Ich = 1000/Rp 200mA->4.99k 400mA->4.99k || 4.99k
I2CEXT0_SCL_in
HSPICLK_in/_out
Ethernet
VSPIQ_in/_out
VSPICLK_in/_out
In RMII Mode
1.8V
MTDI/GPIO12:
I2CEXT1_SCL_out
GPIO4:
EMAC_MDI_in
MTDO/GPIO15:
Signal
LiPo Charger
VSPI_CS2_out
VSPID_in/_out
GPIO2
For more information refer to esp_wroom_32_datasheet_en.pdf.
EMAC_MDC_out
Falling-edge:Input
General Purpose SPI
Voltage of Internal LDO(VDD_SDIO)
HSPIQ_in/_out
Mounting Holes
GPIO5
Falling-edge:Output
EMAC_COL_out

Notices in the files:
projects/olimex_esp32_devkit_lipo_esp32_devkit_lipo_rev_b/current_version/working/working.kicad_pcb:
Rev_B (C)2019
projects/olimex_esp32_evb_esp32_evb_rev_a/current_version/working/working.kicad_pcb:
(C) 2016
